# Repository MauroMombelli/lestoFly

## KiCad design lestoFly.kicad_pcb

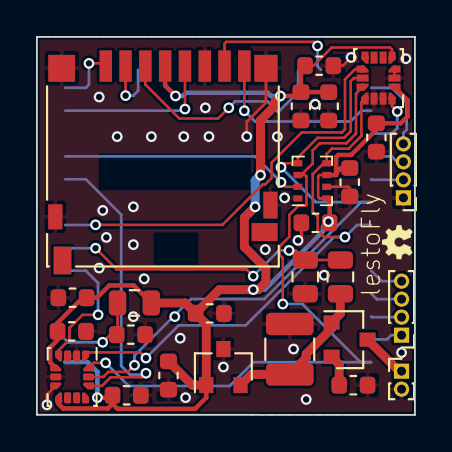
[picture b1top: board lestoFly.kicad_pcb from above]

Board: 2 copper layers, 21.0 x 21.0 mm, 27 parts (1 on the bottom side), 28 nets.

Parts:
C1, C5, C7, C8, C9, C10, C11, C12, C13: 100nF; C_0603_1608Metric
C2, C6: 10uF; C_0603_1608Metric
C3: 0.1uF; C_1210_3225Metric
C4: 0.1uF; C_0603_1608Metric
J1: Conn_01x02_Male; PinHeader_1x02_P1.00mm_Vertical
J3: Conn_01x04_Male; PinHeader_1x04_P1.00mm_Vertical
J4: Conn_01x04_Male; PinHeader_1x04_P1.00mm_Vertical_small
J5: Micro_SD_Card_Det; microSD_HC_Hirose_DM3D-SF
Q1: ZXMP6A13F; SOT-23
R1: 10K; R_0805_2012Metric
R2: 18K; R_0805_2012Metric
R3: 1.5K; R_0805_2012Metric
R5: 12K; C_0603_1608Metric
U1: ESP32-WROOM-32D; ESP32-WROOM-32
U2: LM3480-3.3; SOT-23
U3: BMP280; Bosch_LGA-8_2x2.5mm_P0.65mm_ClockwisePinNumbering
U5, U6: BMX160; LGA-14_3x2.5mm_P0.5mm_LayoutBorder3x4y

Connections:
1: J3.1, U1.36
2: J3.2, U1.35
3: J3.3, U1.34
4: J3.4, U1.33
5: J4.2, U1.29
6: J4.3, U1.28
7: J4.4, U1.25
+3V3: C1.1, C2.1, C4.1, C5.1, C6.1, C7.1, C8.1, C9.1, C10.1, C11.1, C12.1, J5.4, R1.1, U1.2, U2.1, U3.6, U3.8, U5.5, U5.8, U6.5, U6.8
BAT_SCALED: R2.2, R3.1, U1.7
CLK: U1.30, U3.4, U5.13, U6.13
CS_BARO: U1.11, U3.2
CS_IMU_1: U1.10, U6.12
CS_IMU_2: U1.8, U5.12
GND: C1.2, C2.2, C3.2, C4.2, C5.2, C6.2, C7.2, C8.2, C9.2, C10.2, C11.2, C12.2, C13.2, J1.2, J4.1, J5.6, J5.11, R3.2, R5.2, U1.1, U1.15, U1.38, U2.3, U3.1, U3.7, U5.2, U5.3, U5.6, U5.7, U6.2, U6.3, U6.6, U6.7
INT_IMU_1: U1.6, U6.4
INT_IMU_2: U1.27, U5.4
MISO: U1.31, U3.5, U5.1, U6.1
MOSI: U1.37, U3.3, U5.14, U6.14
unnamed: C13.1, R1.2, U1.3
unnamed: J1.1, Q1.3
unnamed: Q1.2, R5.1
SD_CLK: J5.5, U1.13
SD_CMD: J5.3, U1.23
SD_DAT0: J5.7, U1.24
SD_DAT1: J5.8, U1.26
SD_DAT2: J5.1, U1.14
SD_DAT3: J5.2, U1.16
VCC: C3.1, Q1.1, R2.1, U2.2

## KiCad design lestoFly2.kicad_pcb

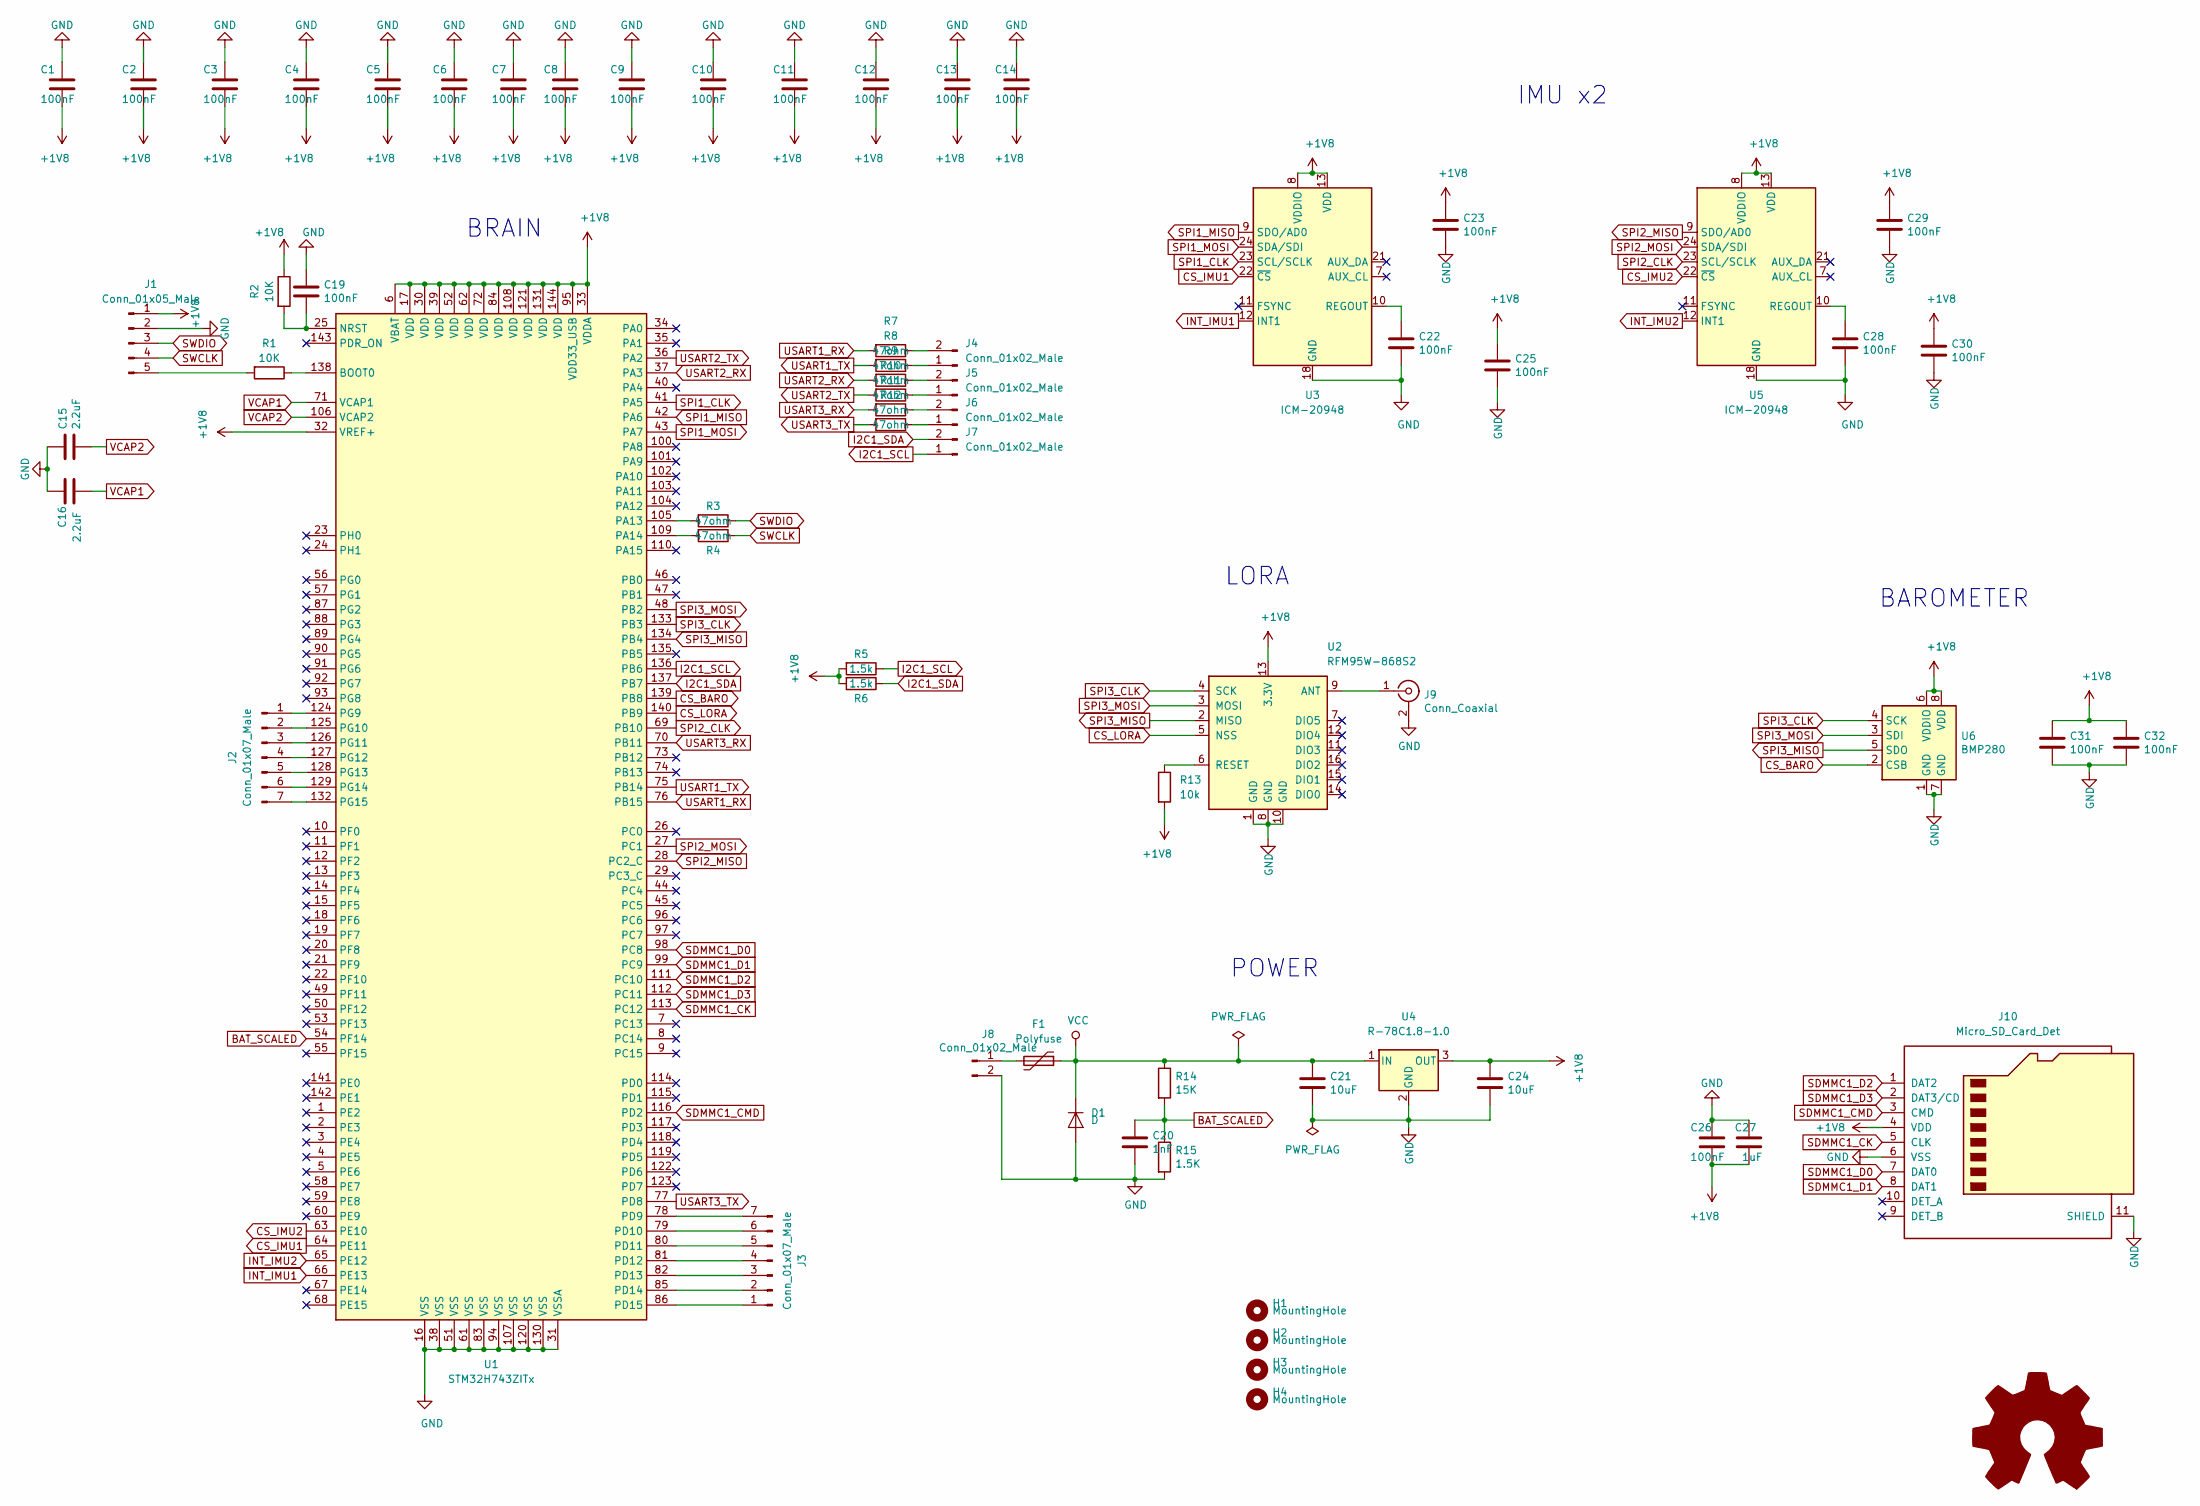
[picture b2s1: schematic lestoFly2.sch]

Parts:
C1, C2, C3, C4, C5, C6, C7, C8, C9, C10, C11, C12, C13, C14, C19, C22, C23, C25, C26, C28, C29, C30, C31, C32: 100nF; C_0603_1608Metric
C15, C16: 2.2uF; C_0603_1608Metric
C20: 1nF; C_0603_1608Metric
C21: 10uF; R_0805_2012Metric
C24: 10uF; C_0603_1608Metric
C27: 1uF; C_0603_1608Metric
D1: D; D_1210_3225Metric
F1: Polyfuse; Fuse_1210_3225Metric
H1, H2, H3, H4: MountingHole; MountingHole_2.2mm_M2
J1: Conn_01x05_Male; PinHeader_1x05_P1.00mm_Vertical
J2, J3: Conn_01x07_Male; PinHeader_1x07_P1.00mm_Vertical
J4, J5, J6, J7, J8: Conn_01x02_Male; PinHeader_1x02_P1.00mm_Vertical
J9: Conn_Coaxial; U.FL_Molex_MCRF_73412-0110_Vertical
J10: Micro_SD_Card_Det; microSD_HC_Hirose_DM3D-SF
R1, R2: 10K; R_0603_1608Metric
R3, R4, R7, R8, R9, R10, R11, R12: 47ohm; R_0603_1608Metric
R5, R6: 1.5k; R_0603_1608Metric
R13: 10k; R_0603_1608Metric
R14: 15K; R_0603_1608Metric
R15: 1.5K; R_0603_1608Metric
U1: STM32H743ZITx; LQFP-144_20x20mm_P0.5mm
U2: RFM95W-868S2; HOPERF_RFM9XW_SMD
U3, U5: ICM-20948; InvenSense_QFN-24_3x3mm_P0.4mm
U4: R-78C1.8-1.0; Converter_DCDC_RECOM_R-78E-0.5_THT
U6: BMP280; Bosch_LGA-8_2x2.5mm_P0.65mm_ClockwisePinNumbering

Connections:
+1V8: C1.2, C2.2, C3.2, C4.2, C5.2, C6.2, C7.2, C8.2, C9.2, C10.2, C11.2, C12.2, C13.2, C14.2, C23.1, C24.1, C25.1, C26.2, C27.2, C29.1, C30.1, C31.1, C32.1, J1.1, J10.4 (VDD), R2.1, R5.2, R6.2, R13.2, U1.6 (VBAT), U1.17 (VDD), U1.30 (VDD), U1.32 (VREF+), U1.33 (VDDA), U1.39 (VDD), U1.52 (VDD), U1.62 (VDD), U1.72 (VDD), U1.84 (VDD), U1.95 (VDD33_USB), U1.108 (VDD), U1.121 (VDD), U1.131 (VDD), U1.144 (VDD), U2.13 (3.3V), U3.8 (VDDIO), U3.13 (VDD), U4.3 (OUT), U5.8 (VDDIO), U5.13 (VDD), U6.6 (VDDIO), U6.8 (VDD)
BAT_SCALED: C20.1, R14.2, R15.1, U1.54 (PF14)
CS_BARO: U1.139 (PB8), U6.2 (CSB)
CS_IMU1: U1.64 (PE11), U3.22 (~CS)
CS_IMU2: U1.63 (PE10), U5.22 (~CS)
CS_LORA: U1.140 (PB9), U2.5 (NSS)
GND: C1.1, C2.1, C3.1, C4.1, C5.1, C6.1, C7.1, C8.1, C9.1, C10.1, C11.1, C12.1, C13.1, C14.1, C15.1, C16.1, C19.1, C20.2, C21.2, C22.2, C23.2, C24.2, C25.2, C26.1, C27.1, C28.2, C29.2, C30.2, C31.2, C32.2, D1.2 (A), J1.2, J8.2, J9.2 (Ext), J10.6 (VSS), J10.11 (SHIELD), R15.2, U1.16 (VSS), U1.31 (VSSA), U1.38 (VSS), U1.51 (VSS), U1.61 (VSS), U1.83 (VSS), U1.94 (VSS), U1.107 (VSS), U1.120 (VSS), U1.130 (VSS), U2.1 (GND), U2.8 (GND), U2.10 (GND), U3.18 (GND), U3.20 (GND), U4.2 (GND), U5.18 (GND), U5.20 (GND), U6.1 (GND), U6.7 (GND)
I2C1_SCL: J7.1, R5.1, U1.136 (PB6)
I2C1_SDA: J7.2, R6.1, U1.137 (PB7)
INT_IMU1: U1.66 (PE13), U3.12 (INT1)
INT_IMU2: U1.65 (PE12), U5.12 (INT1)
unnamed: C19.2, R2.2, U1.25 (NRST)
unnamed: C22.1, U3.10 (REGOUT)
unnamed: C28.1, U5.10 (REGOUT)
unnamed: F1.2, J8.1
unnamed: J1.5, R1.2
unnamed: J2.1, U1.124 (PG9)
unnamed: J2.2, U1.125 (PG10)
unnamed: J2.3, U1.126 (PG11)
unnamed: J2.4, U1.127 (PG12)
unnamed: J2.5, U1.128 (PG13)
unnamed: J2.6, U1.129 (PG14)
unnamed: J2.7, U1.132 (PG15)
unnamed: J3.1, U1.86 (PD15)
unnamed: J3.2, U1.85 (PD14)
unnamed: J3.3, U1.82 (PD13)
unnamed: J3.4, U1.81 (PD12)
unnamed: J3.5, U1.80 (PD11)
unnamed: J3.6, U1.79 (PD10)
unnamed: J3.7, U1.78 (PD9)
unnamed: J4.1, R8.1
unnamed: J4.2, R7.1
unnamed: J5.1, R10.1
unnamed: J5.2, R9.1
unnamed: J6.1, R12.1
unnamed: J6.2, R11.1
unnamed: J9.1 (In), U2.9 (ANT)
unnamed: R1.1, U1.138 (BOOT0)
unnamed: R3.2, U1.105 (PA13)
unnamed: R4.2, U1.109 (PA14)
unnamed: R13.1, U2.6 (RESET)
SDMMC1_CK: J10.5 (CLK), U1.113 (PC12)
SDMMC1_CMD: J10.3 (CMD), U1.116 (PD2)
SDMMC1_D0: J10.7 (DAT0), U1.98 (PC8)
SDMMC1_D1: J10.8 (DAT1), U1.99 (PC9)
SDMMC1_D2: J10.1 (DAT2), U1.111 (PC10)
SDMMC1_D3: J10.2 (DAT3/CD), U1.112 (PC11)
SPI1_CLK: U1.41 (PA5), U3.23 (SCL/SCLK)
SPI1_MISO: U1.42 (PA6), U3.9 (SDO/AD0)
SPI1_MOSI: U1.43 (PA7), U3.24 (SDA/SDI)
SPI2_CLK: U1.69 (PB10), U5.23 (SCL/SCLK)
SPI2_MISO: U1.28 (PC2_C), U5.9 (SDO/AD0)
SPI2_MOSI: U1.27 (PC1), U5.24 (SDA/SDI)
SPI3_CLK: U1.133 (PB3), U2.4 (SCK), U6.4 (SCK)
SPI3_MISO: U1.134 (PB4), U2.2 (MISO), U6.5 (SDO)
SPI3_MOSI: U1.48 (PB2), U2.3 (MOSI), U6.3 (SDI)
SWCLK: J1.4, R4.1
SWDIO: J1.3, R3.1
USART1_RX: R7.2, U1.76 (PB15)
USART1_TX: R8.2, U1.75 (PB14)
USART2_RX: R9.2, U1.37 (PA3)
USART2_TX: R10.2, U1.36 (PA2)
USART3_RX: R11.2, U1.70 (PB11)
USART3_TX: R12.2, U1.77 (PD8)
VCAP1: C16.2, U1.71 (VCAP1)
VCAP2: C15.2, U1.106 (VCAP2)
VCC: C21.1, D1.1 (K), F1.1, R14.1, U4.1 (IN)

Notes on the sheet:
POWER
BAROMETER
IMU x2
LORA
BRAIN

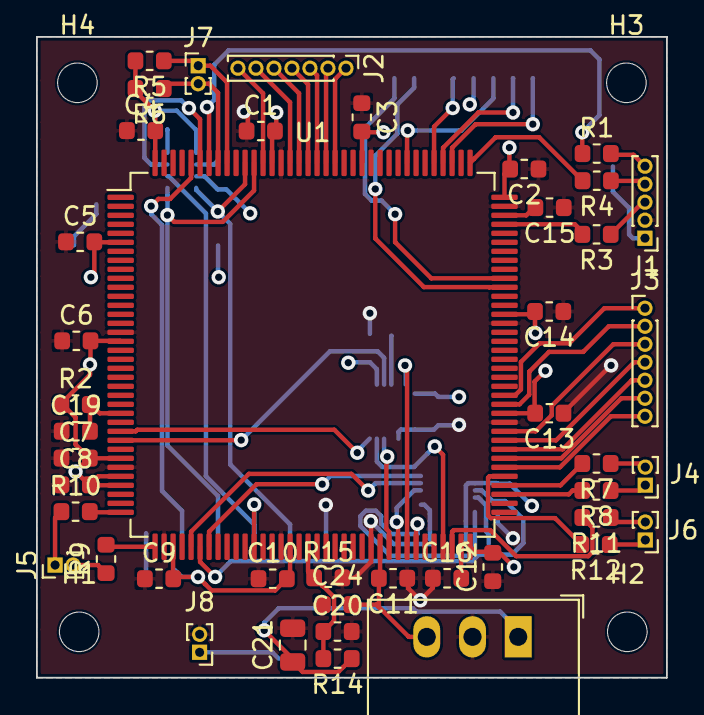
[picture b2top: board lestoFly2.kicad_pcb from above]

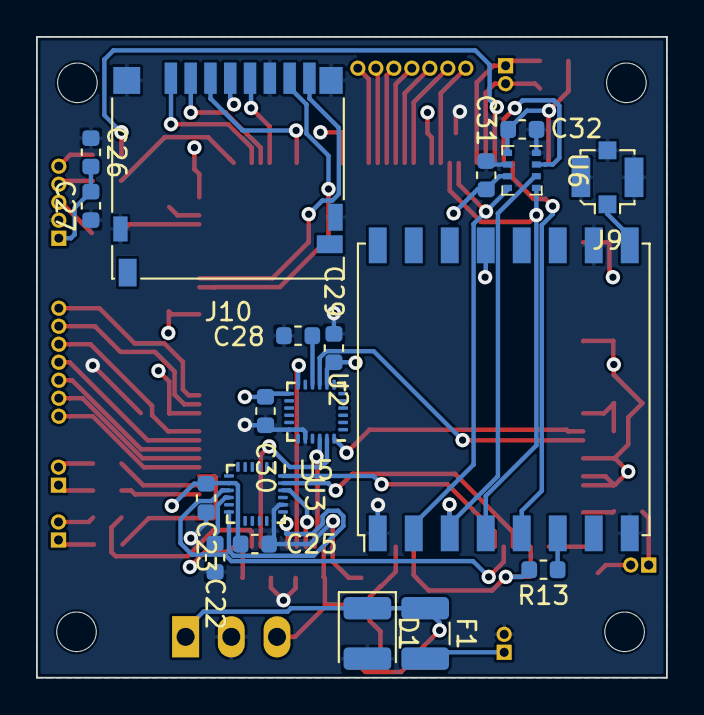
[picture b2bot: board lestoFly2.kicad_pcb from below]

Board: 4 copper layers, 35.0 x 35.6 mm, 67 parts (19 on the bottom side), 67 nets.

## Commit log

2019-05-30 first comit
2019-06-02 board pcb redraw
2019-06-03 new review finish
2019-09-30 completed lestoFly2
2019-09-30 added lestoFly2
2019-10-03 fixed holes to be Naze32 compatible
2019-11-19 varius fixes
2020-02-26 revived esp32
2020-05-09 completed the esp32 version
